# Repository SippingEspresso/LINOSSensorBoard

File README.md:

# LINOSSensorBoard
Senior Design Project by Alex Zahabizadeh, Hailey Lewis, Nikki Shah, Andrew Watts, and Divas Kapur.

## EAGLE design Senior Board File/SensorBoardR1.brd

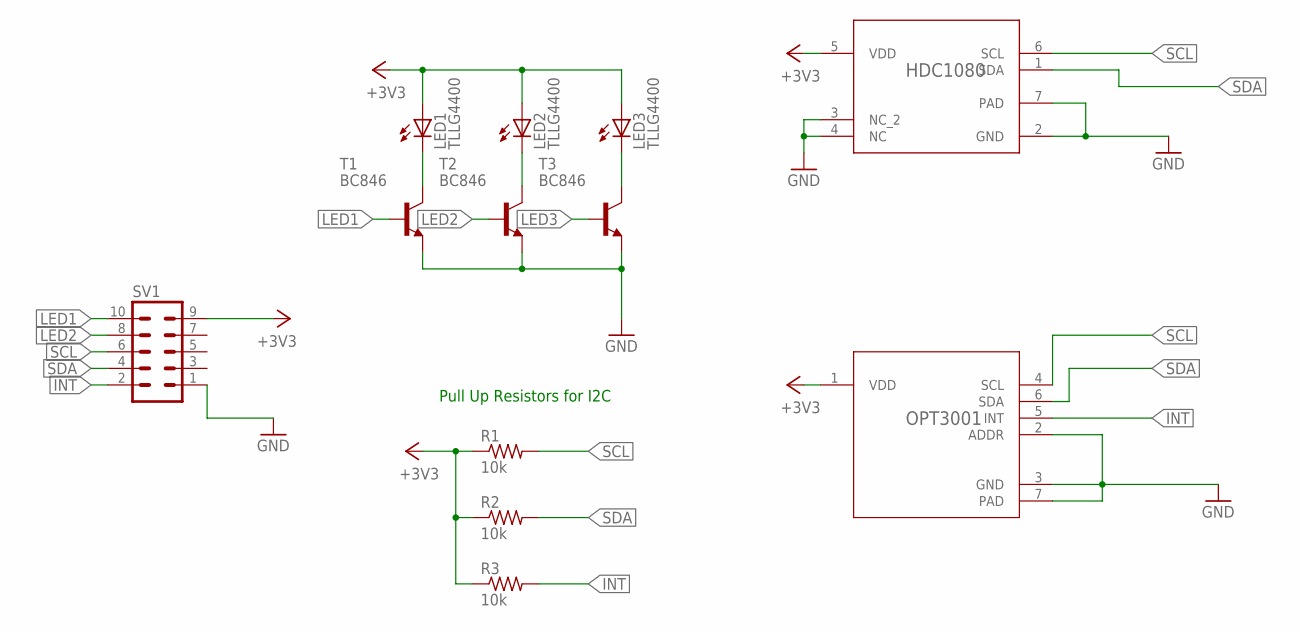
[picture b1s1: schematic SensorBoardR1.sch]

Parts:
HDC1080: HDC1080DMBR; DMB0006A
LED1, LED2, LED3: TLLG4400; LED3MM
OPT3001: OPT3001DNPR; DNP0006A
R1, R2, R3: 10k; R0805
SV1: MA05-2
T1, T2, T3: BC846; SOT23

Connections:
+3V3: HDC1080.5 (VDD), LED1.A, LED2.A, LED3.A, OPT3001.1 (VDD), R1.1, R2.1, R3.1, SV1.9
GND: HDC1080.2 (GND), HDC1080.3 (NC_2), HDC1080.4 (NC), HDC1080.7 (PAD), OPT3001.2 (ADDR), OPT3001.3 (GND), OPT3001.7 (PAD), SV1.1, T1.2 (E), T2.2 (E), T3.2 (E)
INT: OPT3001.5 (INT), R3.2, SV1.2
LED1: SV1.10, T1.1 (B)
LED2: SV1.8, T2.1 (B)
LED3: T3.1 (B)
unnamed: LED3.K (C), T3.3 (C)
unnamed: LED2.K (C), T2.3 (C)
unnamed: LED1.K (C), T1.3 (C)
SCL: HDC1080.6 (SCL), OPT3001.4 (SCL), R1.2, SV1.6
SDA: HDC1080.1 (SDA), OPT3001.6 (SDA), R2.2, SV1.4

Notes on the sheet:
Pull Up Resistors for I2C

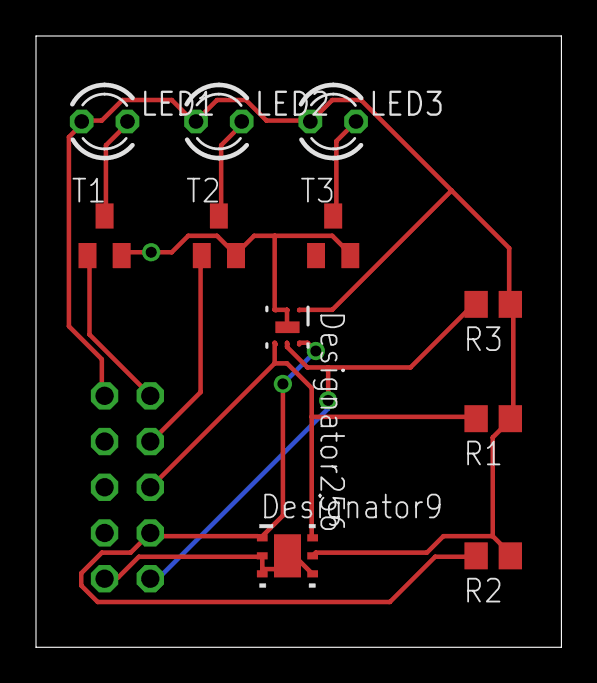
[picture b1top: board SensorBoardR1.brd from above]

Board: 2 copper layers, 29.2 x 34.0 mm, 12 parts (1 on the bottom side), 10 nets.

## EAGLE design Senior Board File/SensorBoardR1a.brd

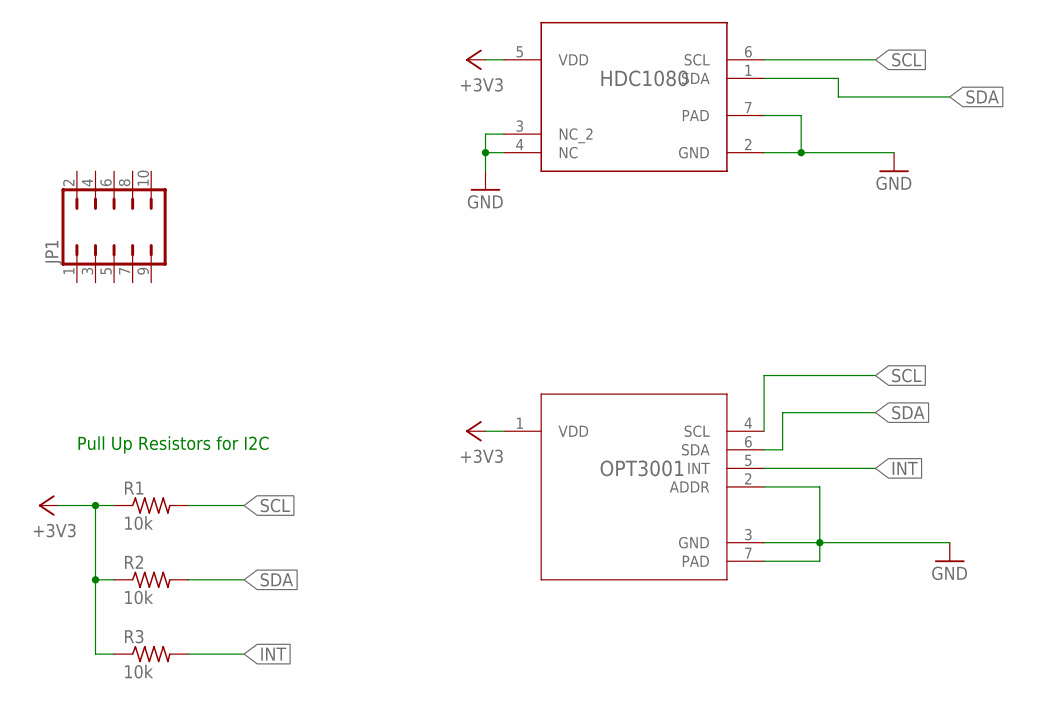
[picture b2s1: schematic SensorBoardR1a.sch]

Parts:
HDC1080: HDC1080DMBR; DMB0006A
JP1: JP5Q
OPT3001: OPT3001DNPR; DNP0006A
R1, R2, R3: 10k; R0805

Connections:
+3V3: HDC1080.5 (VDD), OPT3001.1 (VDD), R1.1, R2.1, R3.1
GND: HDC1080.2 (GND), HDC1080.3 (NC_2), HDC1080.4 (NC), HDC1080.7 (PAD), OPT3001.2 (ADDR), OPT3001.3 (GND), OPT3001.7 (PAD)
INT: OPT3001.5 (INT), R3.2
SCL: HDC1080.6 (SCL), OPT3001.4 (SCL), R1.2
SDA: HDC1080.1 (SDA), OPT3001.6 (SDA), R2.2

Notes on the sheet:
Pull Up Resistors for I2C

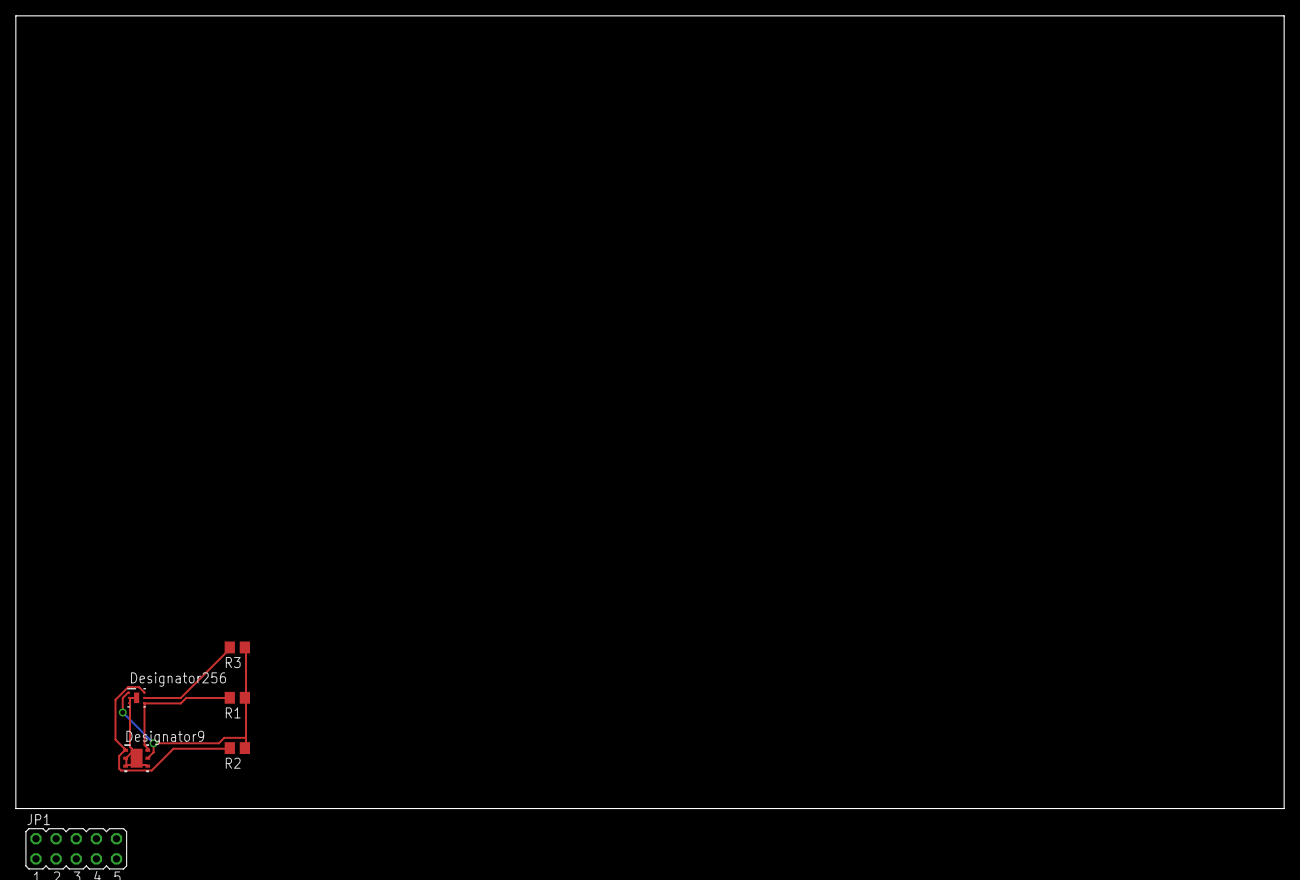
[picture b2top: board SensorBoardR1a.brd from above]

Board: 2 copper layers, 160.0 x 100.0 mm, 6 parts (0 on the bottom side), 5 nets.

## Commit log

2017-01-20 Added LEDs and Header
2017-01-21 100% Build and Ready for R1 Purchase
    Fixed a single wire that was needed
